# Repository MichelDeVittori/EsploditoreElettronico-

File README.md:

# IT: Esploditore Elettronico
Semplice Esploditore elettronico.
Circuito minimale; IC555, Condensatori di stoccaggio e piccolo materiale 

# EN: Very Simple Electronic Blasting Machine
Very few component; IC555, Bank capacitor and others passivie 

# Tools
Developed with Eagle CAD

# Links
e.g. http://www.ntx-int.com/eng/products/equipment-products/blasting-machines/micko-1-dual

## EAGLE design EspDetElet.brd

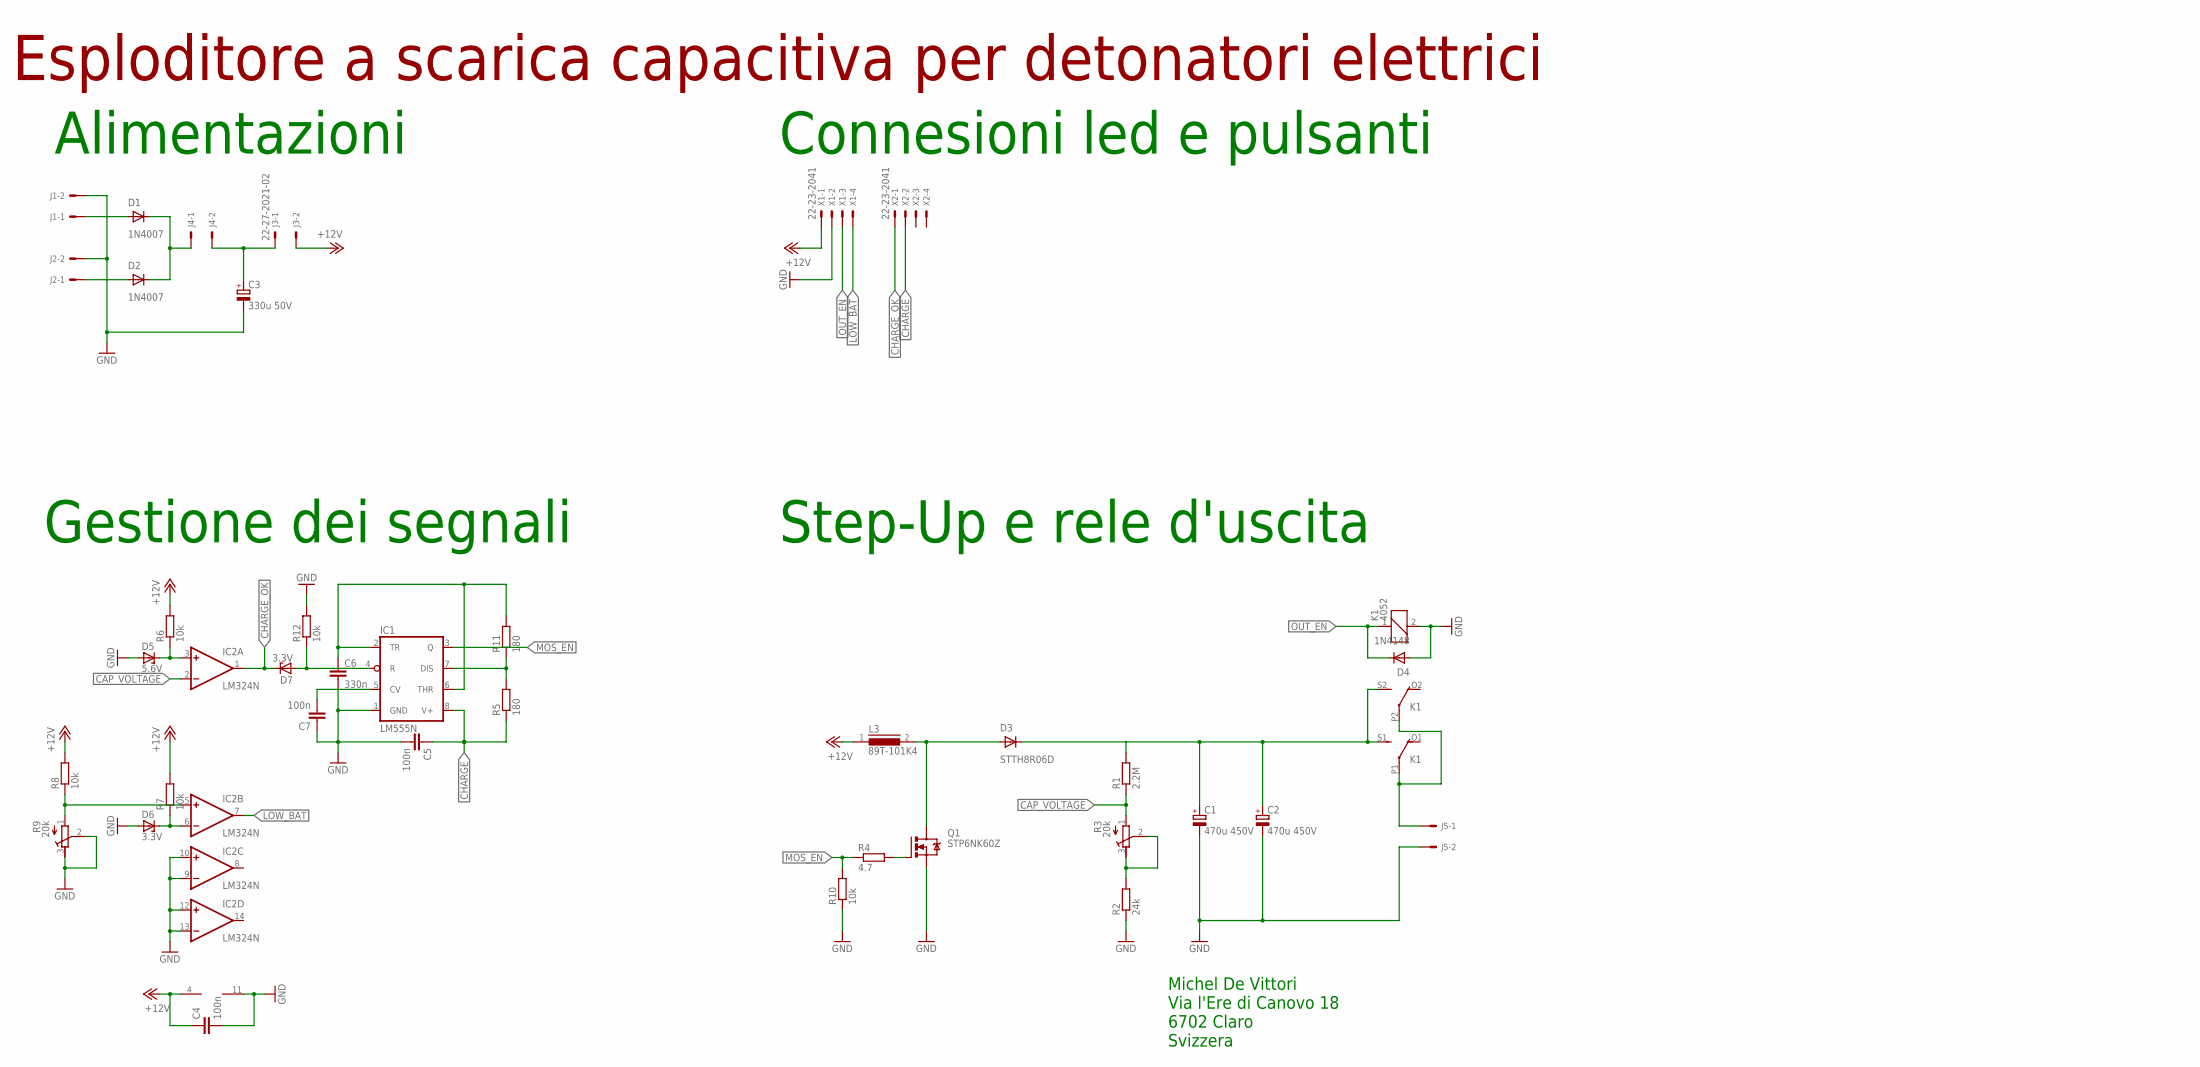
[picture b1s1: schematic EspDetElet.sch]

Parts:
C1, C2: 470u 450V; EB30D
C3: 330u 50V; E5-10,5
C4, C5, C7: 100n; C025-025X050
C6: 330n; C050-030X075
D1, D2: 1N4007; DO41-10
D3: STTH8R06D; TO220ACS
D4: 1N4148; DO35-7
D5: 5.6V; ZDIO-7.5
D6, D7: 3.3V; ZDIO-7.5
IC1: LM555N; DIL08
IC2: LM324N; DIL14
J1, J2, J4, J5: KK-156-2
J3: 22-27-2021-02; 6410-02
K1: 4052; F4052
L3: 89T-101K4; SFT1030
Q1: STP6NK60Z; TO220BV
R1: 2.2M; 0207/10
R2: 24k; 0207/10
R3, R9: 20k; RTRIM64W
R4: 4.7; 0207/10
R5, R11: 180; 0207/10
R6, R7, R8, R10, R12: 10k; 0207/10
X1, X2: 22-23-2041

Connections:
+12V: C4.1, IC2.4 (V+), J3.2, L3.1, R6.2, R7.2, R8.2, X1.1
CAP_VOLTAGE: IC2.2 (-IN), R1.1, R3.1 (E)
CHARGE: C5.1, IC1.8 (V+), R5.1, X2.2
CHARGE_OK: D7.C, IC2.1 (OUT), X2.1
GND: C1.-, C2.-, C3.-, C4.2, C5.2, C6.2, C7.1, D4.A, D5.A, D6.A, IC1.1 (GND), IC2.9 (-IN), IC2.10 (+IN), IC2.11 (V-), IC2.12 (+IN), IC2.13 (-IN), J1.2, J2.2, J5.2, K1.2, Q1.S, R2.1, R9.2 (S), R9.3 (A), R10.1, R12.2, X1.2
LOW_BAT: IC2.7 (OUT), X1.4
MOS_EN: IC1.3 (Q), R4.1, R10.2
unnamed: C1.+, C2.+, D3.C, K1.S1 (S), K1.S2 (S), R1.2
unnamed: D1.A, J1.1
unnamed: D2.A, J2.1
unnamed: D1.C, D2.C, J4.1
unnamed: D3.A, L3.2, Q1.D
unnamed: R2.2, R3.2 (S), R3.3 (A)
unnamed: C3.+, J3.1, J4.2
unnamed: Q1.G, R4.2
unnamed: IC1.7 (DIS), R5.2, R11.1
unnamed: C6.1, IC1.2 (TR), IC1.6 (THR), R11.2
unnamed: C7.2, IC1.5 (CV)
unnamed: D5.C, IC2.3 (+IN), R6.1
unnamed: D7.A, IC1.4 (R), R12.1
unnamed: J5.1, K1.P1, K1.P2
unnamed: D6.C, IC2.6 (-IN), R7.1
unnamed: IC2.5 (+IN), R8.1, R9.1 (E)
OUT_EN: D4.C, K1.1, X1.3

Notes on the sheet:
Michel De Vittori Via l'Ere di Canovo 18 6702 Claro Svizzera
Alimentazioni
Gestione dei segnali
Step-Up e rele d'uscita
Connesioni led e pulsanti
Esploditore a scarica capacitiva per detonatori elettrici

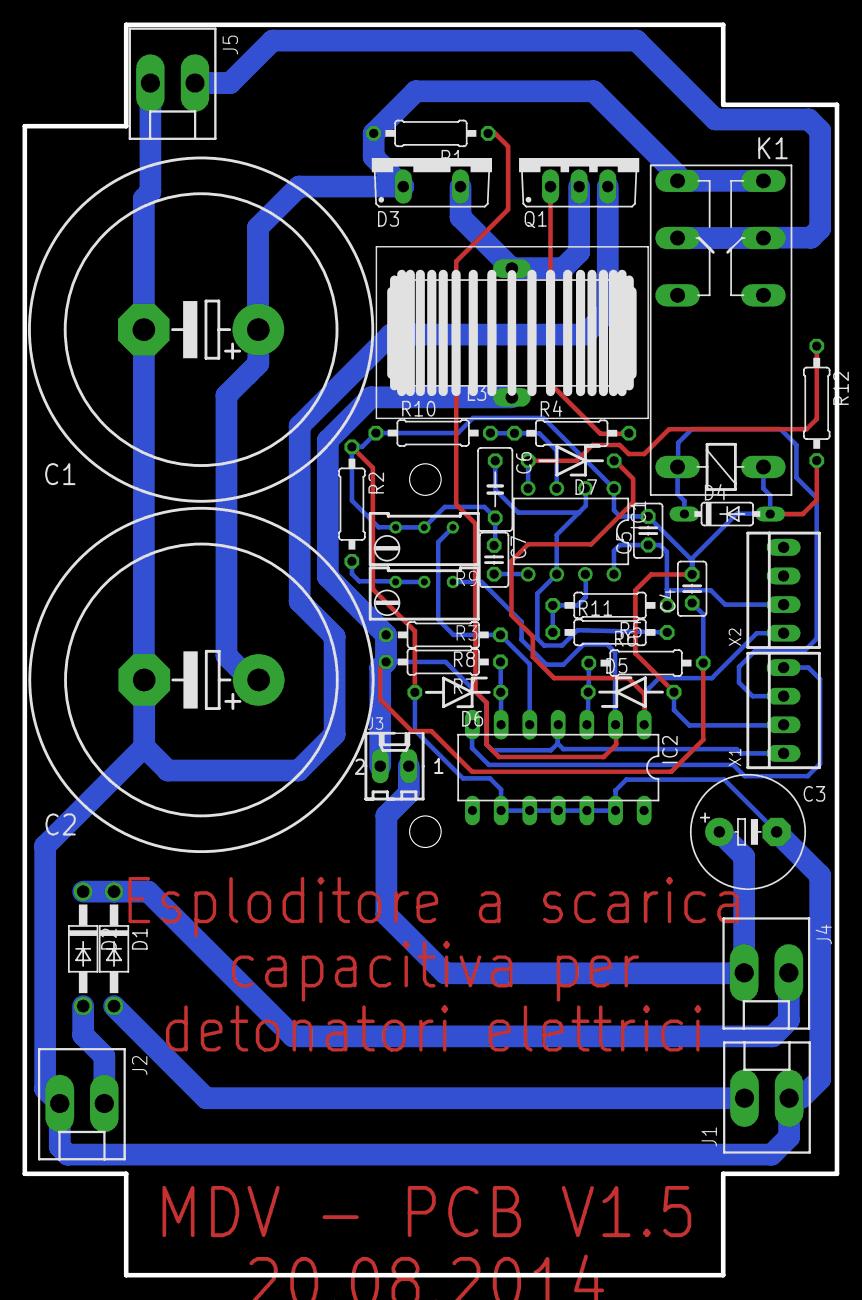
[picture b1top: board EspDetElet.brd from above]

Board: 2 copper layers, 72.1 x 111.0 mm, 38 parts (0 on the bottom side), 24 nets.

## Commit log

2017-11-22 Create LICENSE
